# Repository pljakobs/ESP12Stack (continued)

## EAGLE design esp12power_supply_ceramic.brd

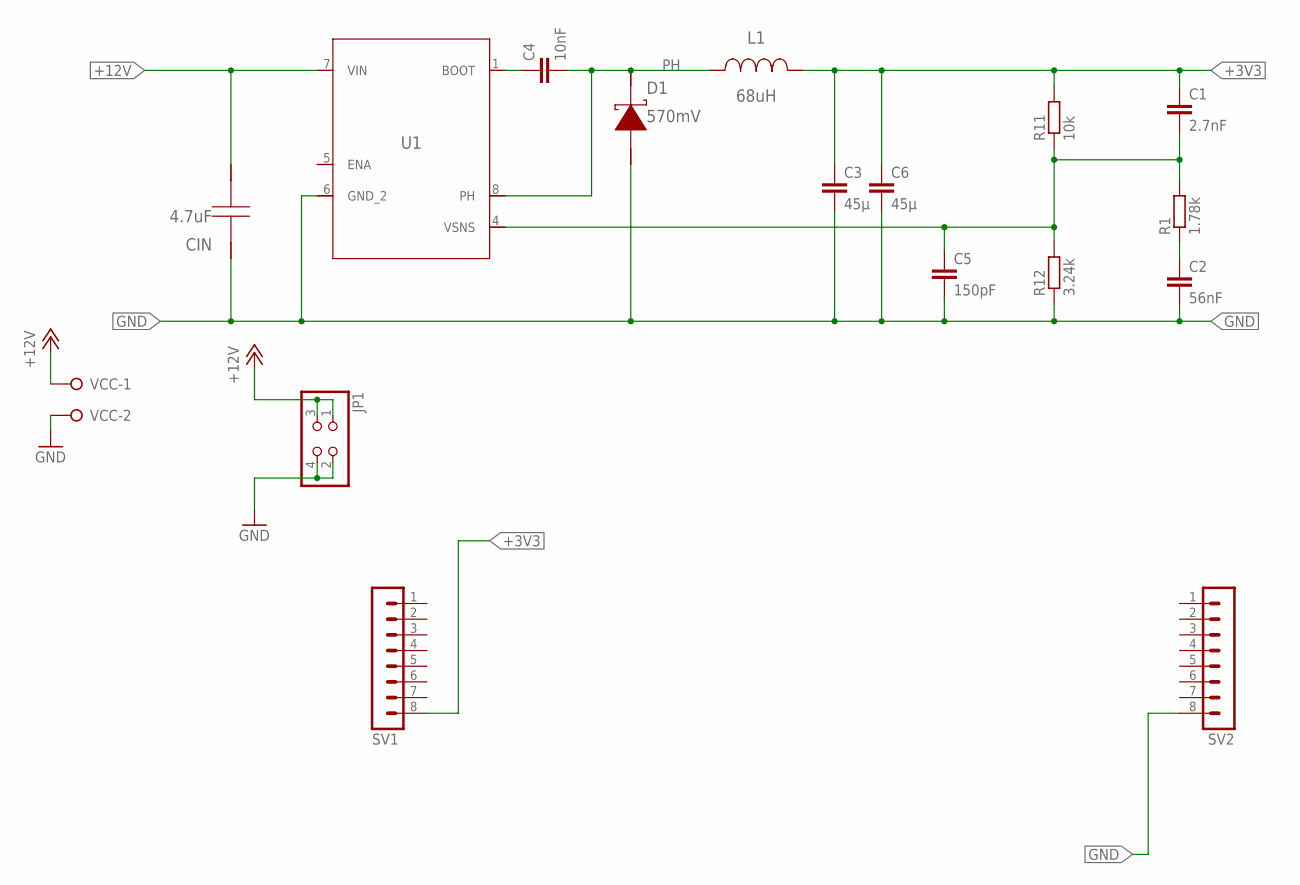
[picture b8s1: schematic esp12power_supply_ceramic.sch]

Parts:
C1: 2.7nF; C0805K
C2: 56nF; C0805K
C3, C6: 45µ; C1210K
C4: 10nF; C0805
C5: 150pF; C0805K
CIN: 4.7uF; 1206
D1: 570mV; SMA
JP1: PINHD-2X2; 2X02
L1: 68uH; IND_NPI75C
R1: 1.78k; R0805
R11: 10k; R0805
R12: 3.24k; R0805
SV1, SV2: MA08-1
U1: TPS5410DR; M08A
VCC: W237-02P; W237-132

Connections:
+3V3: C1.1, C3.1, C6.1, L1.1, R11.2, SV1.8
+12V: CIN.2, JP1.1, JP1.3, U1.7 (VIN), VCC.1
BOOT: C4.1, U1.1 (BOOT)
GND: C2.2, C3.2, C5.2, C6.2, CIN.1, D1.2 (A), JP1.2, JP1.4, R12.1, SV2.8, U1.6 (GND_2), VCC.2
unnamed: C2.1, R1.1
PH: C4.2, D1.1 (K), L1.2, U1.8 (PH)
VSNS: C1.2, C5.1, R1.2, R11.1, R12.2, U1.4 (VSNS)

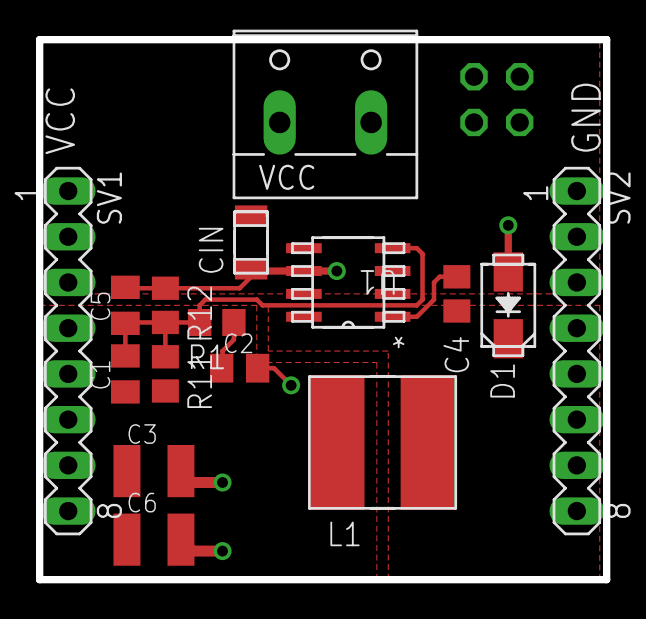
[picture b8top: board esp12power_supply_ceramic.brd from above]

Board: 2 copper layers, 31.5 x 30.0 mm, 17 parts (1 on the bottom side), 7 nets.

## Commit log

2018-12-08 created shields for Power Supply, five channel Mosfet (max 20V7.5A) and general experimentation
2018-12-08 added Gerber/Excellon files
2019-01-09 added an ftdi version
2019-01-10 minor routing changes
2019-01-10 Deep Sleep capability
    added a jumper Position to connect GIPO16 and REST to enable wake up from deep sleep.
2019-09-23 FT232 module
    FT232 Module now functional as a prototype
2019-09-23 initial test with solder jumpers
    added solder jumpers instead of 0603 positions
2019-09-23 optimizing solder jumpers
    different placement for the solder jumpers
2019-10-06 some major updates
    * working ft232rl layout
    * replaced the DIN resistors for the WS2112 with solder jumpers
    * sensors breakout board
    * fixed a bug (missing trace) in the rgbwwpw board
